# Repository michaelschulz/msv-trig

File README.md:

# MS-V Trig

## This circuit is a Eurorack module integrating Korg MS-20 and Eurorack synthesizers.

Eurorack and Korg synthesizers use different control voltages for triggers and gates.
This module bridges the gap by converting Korg S-Triggers into Eurorack CV triggers, 
and Eurorack CV triggers into Korg S-Triggers.

Three CV to S-Trig and two S-trig to CV inputs/ outputs are available.

Schematics and PCB have been designed using KiCad 5.0

The physical layout assumes the 3.5mm jacks to be panel mounted and connected to the 
PCB using wiring, with the sleeve lugs connected between the jacks and finally to GND 
on the PCB.

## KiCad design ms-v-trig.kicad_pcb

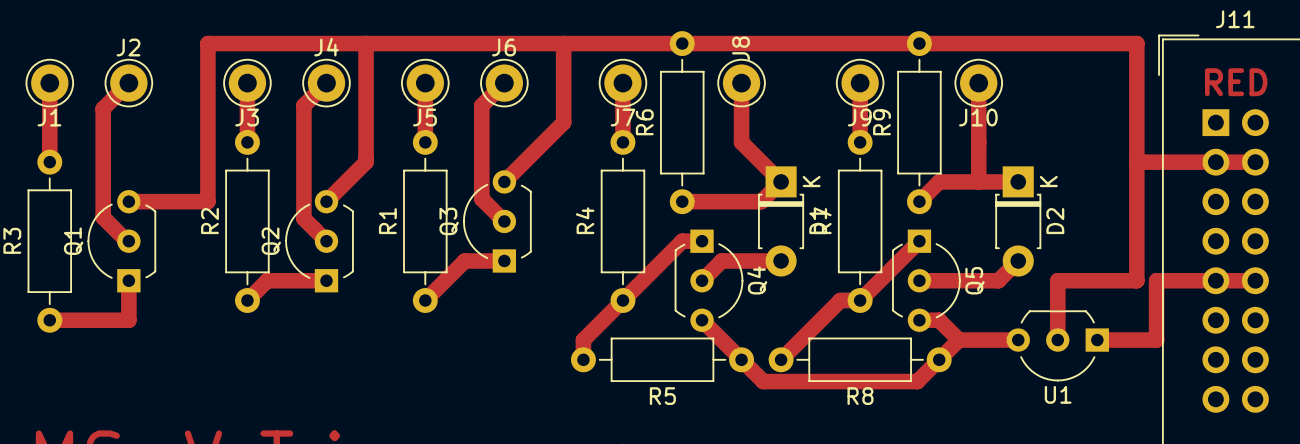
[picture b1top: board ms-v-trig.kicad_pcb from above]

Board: 2 copper layers, 28 parts (0 on the bottom side), 20 nets.

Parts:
D1, D2: 1N4148; D_T-1_P5.08mm_Horizontal
J1: CV IN 1; Pin_D1.0mm_L10.0mm_LooseFit
J2: S TRIG OUT 1; Pin_D1.0mm_L10.0mm_LooseFit
J3: CV IN 2; Pin_D1.0mm_L10.0mm_LooseFit
J4: S TRIG OUT 2; Pin_D1.0mm_L10.0mm_LooseFit
J5: CV IN 3; Pin_D1.0mm_L10.0mm_LooseFit
J6: S TRIG OUT 3; Pin_D1.0mm_L10.0mm_LooseFit
J7: S TRIG IN 1; Pin_D1.0mm_L10.0mm_LooseFit
J8: CV OUT 1; Pin_D1.0mm_L10.0mm_LooseFit
J9: S TRIG IN 2; Pin_D1.0mm_L10.0mm_LooseFit
J10: CV OUT 2; Pin_D1.0mm_L10.0mm_LooseFit
J11: Power Conn; IDC-Header_2x08_P2.54mm_Vertical
Q1, Q2, Q3: Q_NPN_BCE; TO-92L_Inline_Wide
Q4, Q5: Q_PNP_BCE; TO-92L_Inline_Wide
R1, R2, R3, R4, R6, R7, R9: 10k; R_Axial_DIN0207_L6.3mm_D2.5mm_P10.16mm_Horizontal
R5, R8: 100k; R_Axial_DIN0207_L6.3mm_D2.5mm_P10.16mm_Horizontal
U1: LM7805_TO220; TO-92_Inline_Wide

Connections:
GNDPWR: J11.3, J11.4, Q1.3, Q2.3, Q3.3, R6.2, R9.2, U1.2
unnamed: D1.1, J8.1, R6.1
unnamed: D1.2, Q4.2
unnamed: D2.1, J10.1, R9.1
unnamed: D2.2, Q5.2
unnamed: J1.1, R3.2
unnamed: J2.1, Q1.2
unnamed: J3.1, R2.2
unnamed: J4.1, Q2.2
unnamed: J5.1, R1.2
unnamed: J6.1, Q3.2
unnamed: J7.1, R4.2
unnamed: J9.1, R7.2
unnamed: J11.9, J11.10, U1.1
unnamed: Q1.1, R3.1
unnamed: Q2.1, R2.1
unnamed: Q3.1, R1.1
unnamed: Q4.1, R4.1, R5.2
unnamed: Q5.1, R7.1, R8.2
VCC: Q4.3, Q5.3, R5.1, R8.1, U1.3

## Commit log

2018-11-04 Updated PCB
